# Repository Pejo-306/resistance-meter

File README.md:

# Resistance meter

coming soon...

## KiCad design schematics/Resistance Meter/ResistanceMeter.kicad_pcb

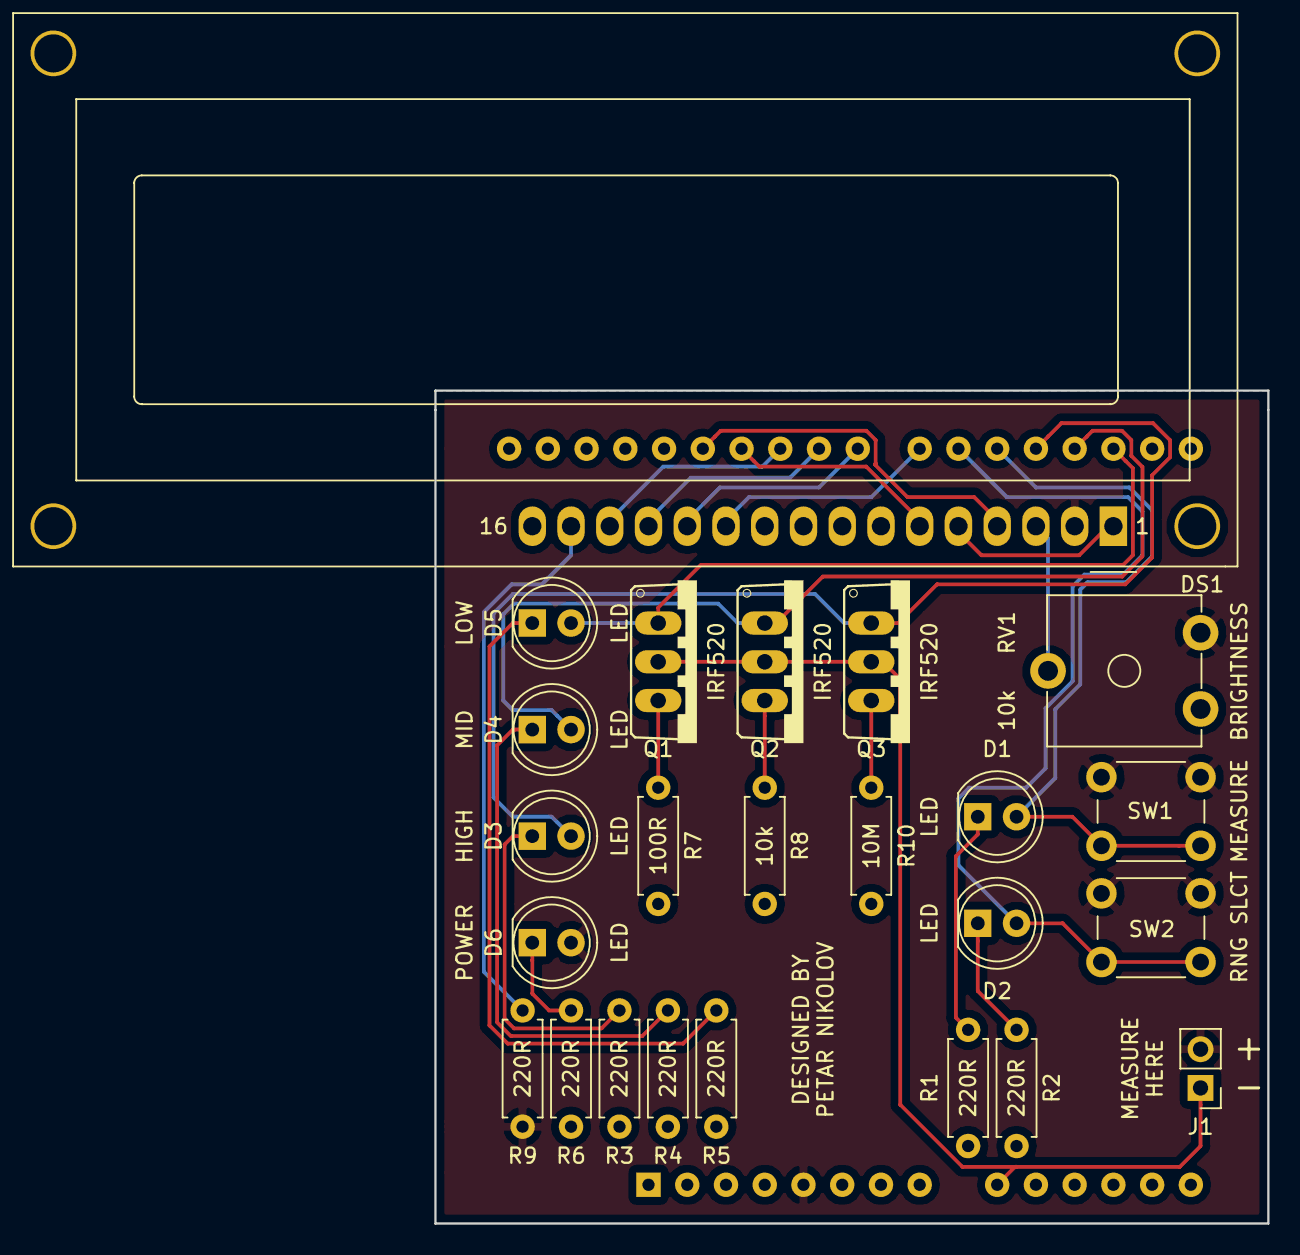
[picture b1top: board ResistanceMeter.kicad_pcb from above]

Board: 2 copper layers, 54.6 x 54.6 mm, 25 parts (1 on the bottom side), 25 nets.

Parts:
A1: Arduino_UNO_R3
D1, D2, D3, D4, D5, D6: LED; LED_D5.0mm
DS1: NDS1602A; WC1602A
J1: Conn_01x02_Male; Pin_Header_Straight_1x02_Pitch2.54mm
Q1, Q2, Q3: IRF520; TO220BV
R1, R2, R3, R4, R5, R6, R9: 220R; R_Axial_DIN0207_L6.3mm_D2.5mm_P7.62mm_Horizontal
R7: 100R; R_Axial_DIN0207_L6.3mm_D2.5mm_P7.62mm_Horizontal
R8: 10k; R_Axial_DIN0207_L6.3mm_D2.5mm_P7.62mm_Horizontal
R10: 10M; R_Axial_DIN0207_L6.3mm_D2.5mm_P7.62mm_Horizontal
RV1: 10k; Potentiometer_Trimmer_ACP_CA9v_Horizontal_Px10.0mm_Py5.0mm
SW1, SW2: SW_Push; SW_PUSH_6mm_h4.3mm

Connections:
+5V: A1.5, D6.2, DS1.2, J1.2, R9.2, RV1.1, SW1.2, SW2.2
/ANALOG_INPUT: A1.9, J1.1, Q1.D, Q2.D, Q3.D
GND: A1.6, A1.7, A1.29, DS1.1, DS1.5, DS1.16, R1.2, R2.2, R3.2, R4.2, R5.2, R6.2, R7.2, R8.2, R10.2, RV1.3
unnamed: A1.17, D5.2, Q1.G
unnamed: A1.18, D4.2, Q2.G
unnamed: A1.19, D3.2, Q3.G
unnamed: A1.20, D1.2, SW1.1
unnamed: A1.21, D2.2, SW2.1
unnamed: A1.22, DS1.11
unnamed: A1.23, DS1.12
unnamed: A1.24, DS1.13
unnamed: A1.25, DS1.14
unnamed: A1.26, DS1.6
unnamed: A1.27, DS1.4
unnamed: D1.1, R1.1
unnamed: D2.1, R2.1
unnamed: D3.1, R3.1
unnamed: D4.1, R4.1
unnamed: D5.1, R5.1
unnamed: D6.1, R6.1
unnamed: DS1.3, RV1.2
unnamed: DS1.15, R9.1
unnamed: Q1.S, R7.1
unnamed: Q2.S, R8.1
unnamed: Q3.S, R10.1

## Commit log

2018-07-05 Add LICENSE
2018-07-05 Commit prototype sketch
2018-07-05 Add .gitignore
2018-07-05 Include prototype schematics
    These schematics the most bare bones design for this project.
2018-07-05 Add final project schematics
2018-07-05 Include circuit analysis calculations
    The spreadsheet contains calculations of the main electrical parameters
    with different reference resistances.
2018-07-05 Modify schematic to not use pin 13 of the Arduino Uno
    Since pin 13 controls the board's built-in LED, I have decided to switch
    the pins so that the 13th one is no longer in use. See the newer
    schematics for more details.
2018-07-06 Implement functionality to select the measuring range
    The reference resistance's value can be selected by pressing the
    RANGE_SELECT switch of the circuit which will select the next measuring
    range. If the button is pressed on the last range, the selection loops
    back and begins anew (i.e. it selects the first range).
2018-07-06 Overload the LCD parameter formatting function
    The new overloaded function returns a decimal number (i.e. a double)
    instead of an integral number which allows for more precise designation
    of the parsed argument.
2018-07-07 Commit a fully functional project sketch
2018-07-09 Finalize the project's schematic
    The PCB layout can now be designed.
    Notes:
    - the folder which contained the schematics had a spelling mistake
    that has been fixed
2018-07-09 Design the PCB for the project
2018-07-17 Completely redo project PCB
2018-07-23 Revise the PCB layout (again)
    Also, changed a few of the design's footprints.
2018-07-31 Update to KiCad 5 from 4
    - use KiCad's standard library Arduino shield symbol and footprint
    - ground the second copper layer of the PCB (and consequently unground
    the first copper layer of the PCB)
2018-08-15 Revise the project's schematic
2018-08-15 Revise the project's PCB design
